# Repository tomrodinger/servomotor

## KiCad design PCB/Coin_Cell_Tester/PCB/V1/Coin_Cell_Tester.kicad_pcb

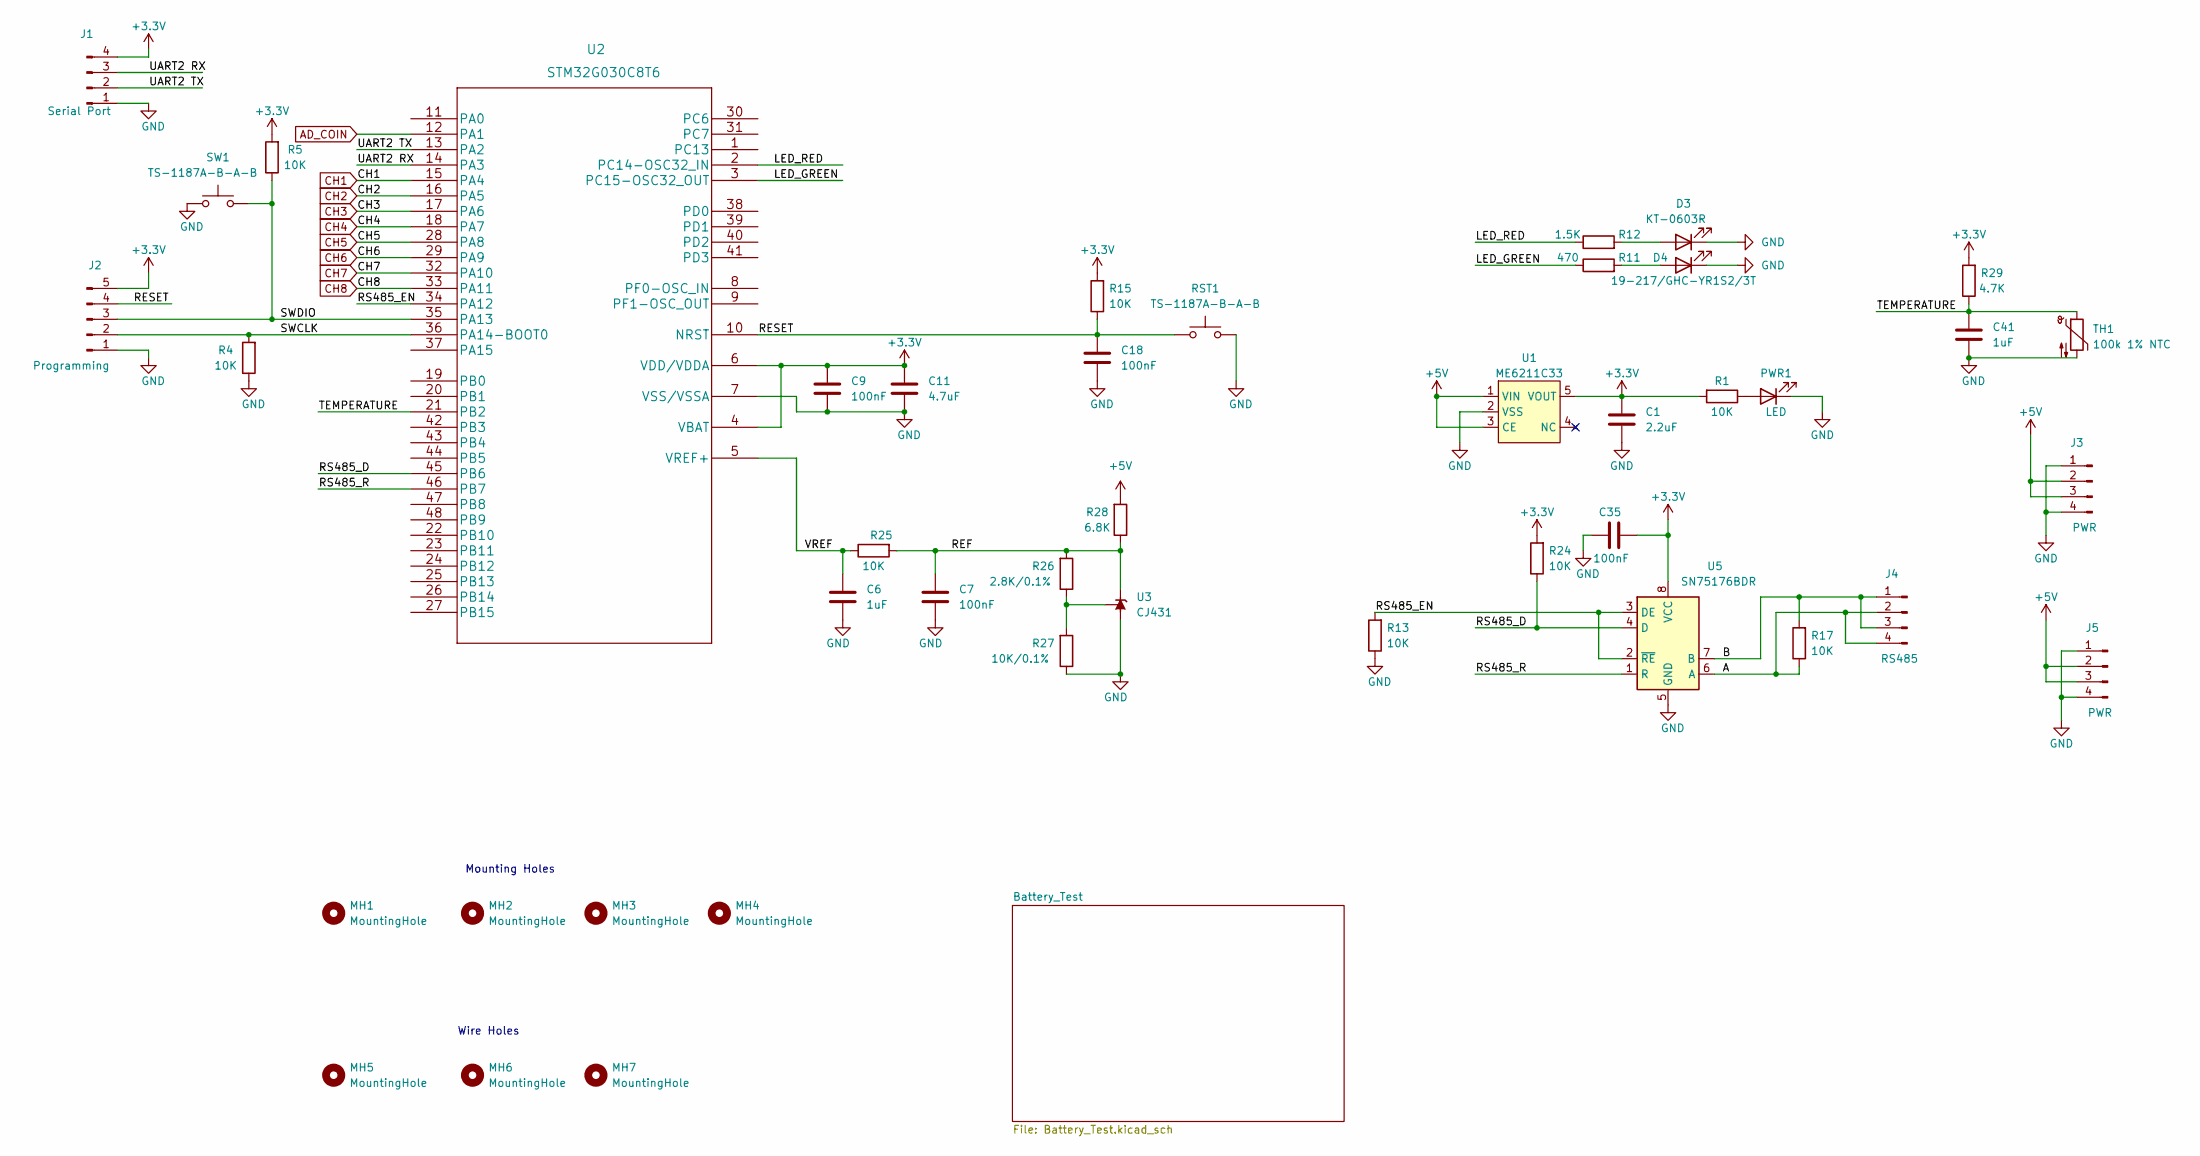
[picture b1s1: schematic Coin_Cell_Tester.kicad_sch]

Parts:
C1: 2.2uF; C_0603_1608Metric
C6, C41: 1uF; C_0603_1608Metric
C7, C9, C18, C35: 100nF; C_0603_1608Metric
C11: 4.7uF; C_0603_1608Metric
D3: KT-0603R; LED_0603_1608Metric
D4: 19-217/GHC-YR1S2/3T; LED_0603_1608Metric
J1: Serial Port; PinHeader_1x04_P2.54mm_Vertical
J2: Programming; PinHeader_1x05_P2.54mm_Vertical
J3, J5: PWR; PinHeader_1x04_P2.54mm_Vertical
J4: RS485; PinHeader_1x04_P2.54mm_Vertical
MH1, MH2, MH3, MH4: MountingHole; MountingHole_3.2mm_M3
MH5, MH6, MH7: MountingHole; Wire hole
PWR1: LED; LED_0603_1608Metric; LCSC PN C434420
R1, R4, R5, R13, R15, R17, R24, R25: 10K; R_0603_1608Metric
R11: 470; R_0603_1608Metric
R12: 1.5K; R_0603_1608Metric
R26: 2.8K/0.1%; R_0402_1005Metric; Mfr PN PTFR0402B2K80P9; LCSC C2692906
R27: 10K/0.1%; R_0603_1608Metric
R28: 6.8K; R_0603_1608Metric
R29: 4.7K; R_0603_1608Metric
RST1: TS-1187A-B-A-B; SW_SPST_TL3342
SW1: TS-1187A-B-A-B; SW_SPST_TL3342
TH1: 100k 1% NTC; R_0402_1005Metric
U1: ME6211C33; SOT-23-5; LCSC PN C82942
U2: STM32G030C8T6; LQFP-48_7x7mm_P0.5mm
U3: CJ431; SOT-23; LCSC C3113
U5: SN75176BDR; SOIC-8_3.9x4.9mm_P1.27mm

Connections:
+3V3: C1.1, C9.1, C11.1, C35.2, J1.4, J2.5, R1.2, R5.2, R15.2, R24.2, R29.2, U1.5 (VOUT), U2.4 (VBAT), U2.6 (VDD/VDDA), U5.8 (VCC)
+5V: J3.2, J3.3, J5.2, J5.3, R28.2, U1.1 (VIN), U1.3 (CE); also elsewhere on the board
/A: J4.2, J4.4, R17.1, U5.6 (A)
/B: J4.1, J4.3, R17.2, U5.7 (B)
/LED_GREEN: R11.1, U2.3 (PC15-OSC32_OUT)
/LED_RED: R12.1, U2.2 (PC14-OSC32_IN)
/REF: C7.1, R25.2, R26.2, R28.1, U3.1 (K)
/RESET: C18.1, J2.4, R15.1, RST1.1, U2.10 (NRST)
/RS485_D: R24.1, U2.45 (PB6), U5.4 (D)
/RS485_EN: R13.2, U2.34 (PA12), U5.2 (~RE), U5.3 (DE)
/RS485_R: U2.46 (PB7), U5.1 (R)
/SWCLK: J2.2, R4.2, U2.36 (PA14-BOOT0)
/SWDIO: J2.3, R5.1, SW1.2, U2.35 (PA13)
/TEMPERATURE: C41.1, R29.1, TH1.1, U2.21 (PB2)
/UART2 RX: J1.3, U2.14 (PA3)
/UART2 TX: J1.2, U2.13 (PA2)
/VREF: C6.1, R25.1, U2.5 (VREF+)
AD_COIN: U2.12 (PA1); also elsewhere on the board
CH1: U2.15 (PA4); also elsewhere on the board
CH2: U2.16 (PA5); also elsewhere on the board
CH3: U2.17 (PA6); also elsewhere on the board
CH4: U2.18 (PA7); also elsewhere on the board
CH5: U2.28 (PA8); also elsewhere on the board
CH6: U2.29 (PA9); also elsewhere on the board
CH7: U2.32 (PA10); also elsewhere on the board
CH8: U2.33 (PA11); also elsewhere on the board
GND: C1.2, C6.2, C7.2, C9.2, C11.2, C18.2, C35.1, C41.2, D3.1 (K), D4.1 (K), J1.1, J2.1, J3.1, J3.4, J5.1, J5.4, PWR1.1 (K), R4.1, R13.1, R27.1, RST1.2, SW1.1, TH1.2, U1.2 (VSS), U2.7 (VSS/VSSA), U3.3 (A), U5.5 (GND); also elsewhere on the board
unnamed: D3.2 (A), R12.2
unnamed: D4.2 (A), R11.2
unnamed: PWR1.2 (A), R1.1
unnamed: R26.1, R27.2, U3.2 (REF)

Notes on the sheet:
Mounting Holes
Wire Holes

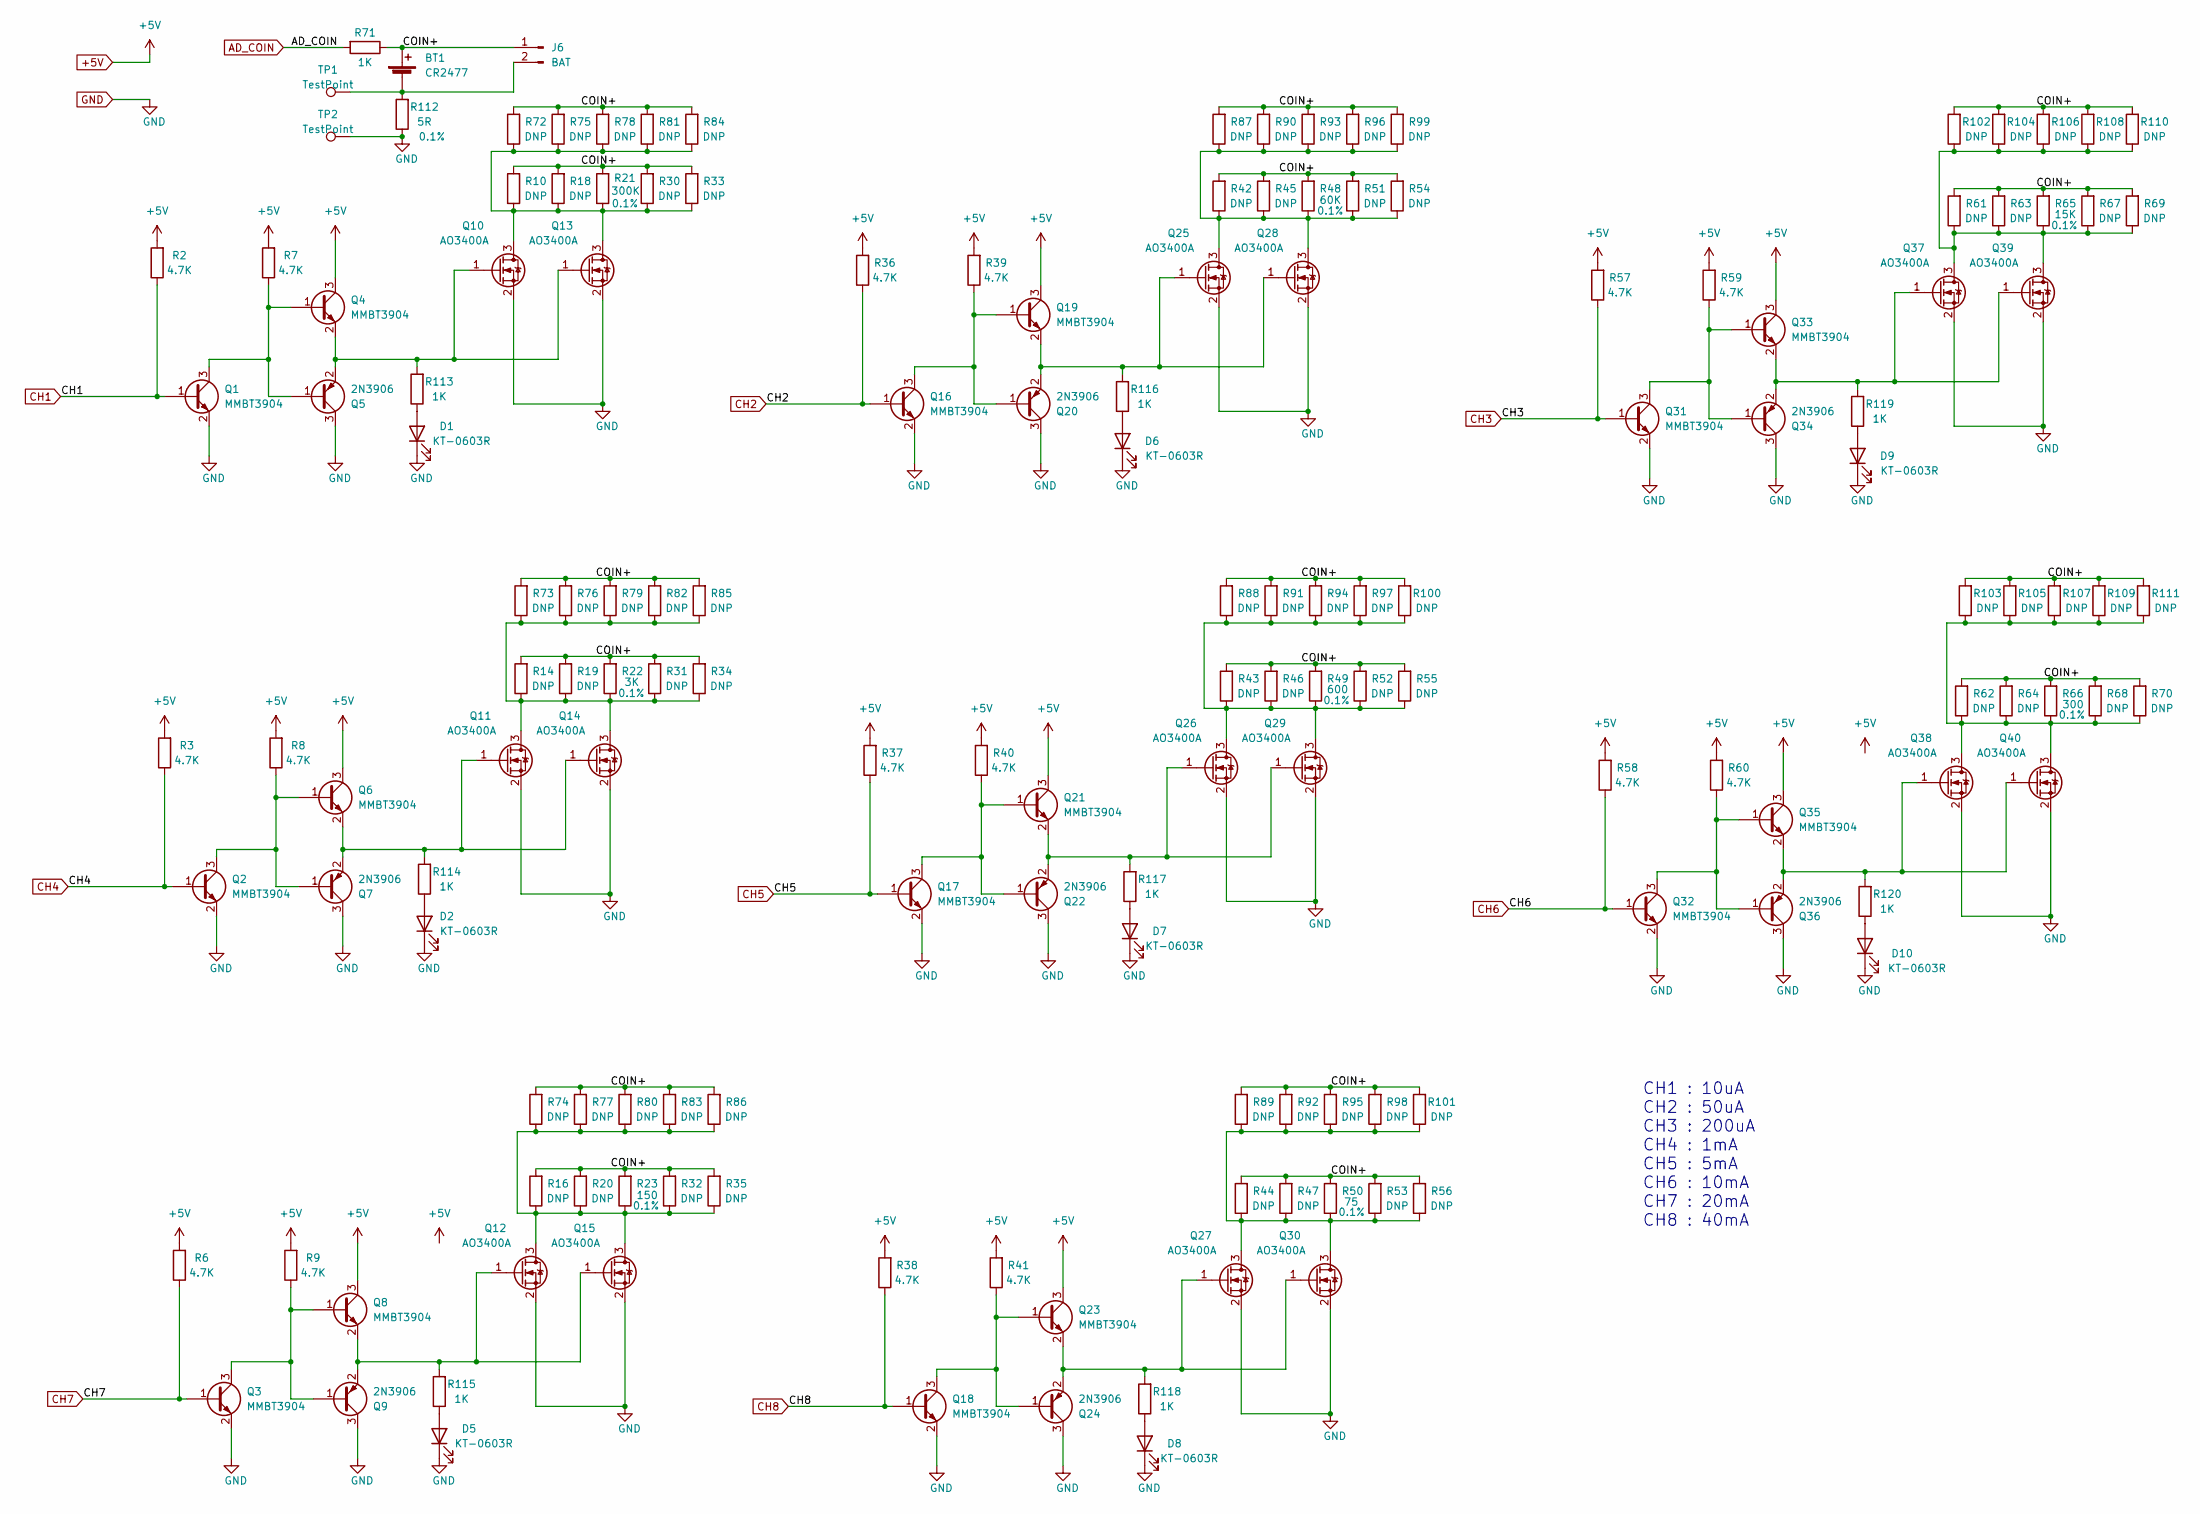
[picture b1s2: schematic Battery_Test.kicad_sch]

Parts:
BT1: CR2477; BatteryHolder_Keystone_105_1x2430; LCSC C969907
D1, D2, D5, D6, D7, D8, D9, D10: KT-0603R; LED_0603_1608Metric
J6: BAT; PinHeader_1x02_P2.54mm_Vertical
Q1, Q2, Q3, Q4, Q6, Q8, Q16, Q17, Q18, Q19, Q21, Q23, Q31, Q32, Q33, Q35: MMBT3904; SOT-23; LCSC C20526
Q5, Q7, Q9, Q20, Q22, Q24, Q34, Q36: 2N3906; SOT-23; LCSC C147294
Q10, Q11, Q12, Q13, Q14, Q15, Q25, Q26, Q27, Q28, Q29, Q30, Q37, Q38, Q39, Q40: AO3400A; SOT-23; LCSC C20917
R2, R3, R6, R7, R8, R9, R36, R37, R38, R39, R40, R41, R57, R58, R59, R60: 4.7K; R_0603_1608Metric
R10, R14, R16, R18, R19, R20, R30, R31, R32, R33, R34, R35, R42, R43, R44, R45, R46, R47, R51, R52, R53, R54, R55, R56, R61, R62, R63, R64, R67, R68, R69, R70: DNP; R_Axial_DIN0207_L6.3mm_D2.5mm_P10.16mm_Horizontal
R21: 300K; R_Axial_DIN0207_L6.3mm_D2.5mm_P10.16mm_Horizontal
R22: 3K; R_Axial_DIN0207_L6.3mm_D2.5mm_P10.16mm_Horizontal
R23: 150; R_Axial_DIN0207_L6.3mm_D2.5mm_P10.16mm_Horizontal
R48: 60K; R_Axial_DIN0207_L6.3mm_D2.5mm_P10.16mm_Horizontal
R49: 600; R_Axial_DIN0207_L6.3mm_D2.5mm_P10.16mm_Horizontal
R50: 75; R_Axial_DIN0207_L6.3mm_D2.5mm_P10.16mm_Horizontal
R65: 15K; R_Axial_DIN0207_L6.3mm_D2.5mm_P10.16mm_Horizontal
R66: 300; R_Axial_DIN0207_L6.3mm_D2.5mm_P10.16mm_Horizontal
R71, R113, R114, R115, R116, R117, R118, R119, R120: 1K; R_0603_1608Metric
R72, R73, R74, R87, R88, R89, R102, R103: DNP; R_0402_1005Metric
R75, R76, R77, R90, R91, R92, R104, R105: DNP; R_0603_1608Metric
R78, R79, R80, R93, R94, R95, R106, R107: DNP; R_0805_2012Metric
R81, R82, R83, R96, R97, R98, R108, R109: DNP; R_1206_3216Metric
R84, R85, R86, R99, R100, R101, R110, R111: DNP; R_1210_3225Metric
R112: 5R; R_Axial_DIN0207_L6.3mm_D2.5mm_P10.16mm_Horizontal
TP1, TP2: TestPoint; TestPoint_Plated_Hole_D2.0mm

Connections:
+5V: Q4.3 (C), Q6.3 (C), Q8.3 (C), Q19.3 (C), Q21.3 (C), Q23.3 (C), Q33.3 (C), Q35.3 (C), R2.2, R3.2, R6.2, R7.2, R8.2, R9.2, R36.2, R37.2, R38.2, R39.2, R40.2, R41.2, R57.2, R58.2, R59.2, R60.2; also elsewhere on the board
/Battery_Test/COIN+: BT1.1 (+), J6.1, R10.2, R14.2, R16.2, R18.2, R19.2, R20.2, R21.2, R22.2, R23.2, R30.2, R31.2, R32.2, R33.2, R34.2, R35.2, R42.2, R43.2, R44.2, R45.2, R46.2, R47.2, R48.2, R49.2, R50.2, R51.2, R52.2, R53.2, R54.2, R55.2, R56.2, R61.2, R62.2, R63.2, R64.2, R65.2, R66.2, R67.2, R68.2, R69.2, R70.2, R71.1, R72.2, R73.2, R74.2, R75.2, R76.2, R77.2, R78.2, R79.2, R80.2, R81.2, R82.2, R83.2, R84.2, R85.2, R86.2, R87.2, R88.2, R89.2, R90.2, R91.2, R92.2, R93.2, R94.2, R95.2, R96.2, R97.2, R98.2, R99.2, R100.2, R101.2, R102.2, R103.2, R104.2, R105.2, R106.2, R107.2, R108.2, R109.2, R110.2, R111.2
AD_COIN: R71.2; also elsewhere on the board
CH1: Q1.1 (B), R2.1; also elsewhere on the board
CH2: Q16.1 (B), R36.1; also elsewhere on the board
CH3: Q31.1 (B), R57.1; also elsewhere on the board
CH4: Q2.1 (B), R3.1; also elsewhere on the board
CH5: Q17.1 (B), R37.1; also elsewhere on the board
CH6: Q32.1 (B), R58.1; also elsewhere on the board
CH7: Q3.1 (B), R6.1; also elsewhere on the board
CH8: Q18.1 (B), R38.1; also elsewhere on the board
GND: D1.1 (K), D2.1 (K), D5.1 (K), D6.1 (K), D7.1 (K), D8.1 (K), D9.1 (K), D10.1 (K), Q1.2 (E), Q2.2 (E), Q3.2 (E), Q5.3 (C), Q7.3 (C), Q9.3 (C), Q10.2 (S), Q11.2 (S), Q12.2 (S), Q13.2 (S), Q14.2 (S), Q15.2 (S), Q16.2 (E), Q17.2 (E), Q18.2 (E), Q20.3 (C), Q22.3 (C), Q24.3 (C), Q25.2 (S), Q26.2 (S), Q27.2 (S), Q28.2 (S), Q29.2 (S), Q30.2 (S), Q31.2 (E), Q32.2 (E), Q34.3 (C), Q36.3 (C), Q37.2 (S), Q38.2 (S), Q39.2 (S), Q40.2 (S), R112.1, TP2.1; also elsewhere on the board
unnamed: BT1.2 (-), J6.2, R112.2, TP1.1
unnamed: D1.2 (A), R113.1
unnamed: D2.2 (A), R114.1
unnamed: D6.2 (A), R116.1
unnamed: Q1.3 (C), Q4.1 (B), Q5.1 (B), R7.1
unnamed: Q2.3 (C), Q6.1 (B), Q7.1 (B), R8.1
unnamed: Q3.3 (C), Q8.1 (B), Q9.1 (B), R9.1
unnamed: Q4.2 (E), Q5.2 (E), Q10.1 (G), Q13.1 (G), R113.2
unnamed: Q10.3 (D), Q13.3 (D), R10.1, R18.1, R21.1, R30.1, R33.1, R72.1, R75.1, R78.1, R81.1, R84.1
unnamed: Q6.2 (E), Q7.2 (E), Q11.1 (G), Q14.1 (G), R114.2
unnamed: Q11.3 (D), Q14.3 (D), R14.1, R19.1, R22.1, R31.1, R34.1, R73.1, R76.1, R79.1, R82.1, R85.1
unnamed: Q8.2 (E), Q9.2 (E), Q12.1 (G), Q15.1 (G), R115.2
unnamed: Q12.3 (D), Q15.3 (D), R16.1, R20.1, R23.1, R32.1, R35.1, R74.1, R77.1, R80.1, R83.1, R86.1
unnamed: Q16.3 (C), Q19.1 (B), Q20.1 (B), R39.1
unnamed: Q17.3 (C), Q21.1 (B), Q22.1 (B), R40.1
unnamed: Q18.3 (C), Q23.1 (B), Q24.1 (B), R41.1
unnamed: Q19.2 (E), Q20.2 (E), Q25.1 (G), Q28.1 (G), R116.2
unnamed: Q21.2 (E), Q22.2 (E), Q26.1 (G), Q29.1 (G), R117.2
unnamed: Q23.2 (E), Q24.2 (E), Q27.1 (G), Q30.1 (G), R118.2
unnamed: Q25.3 (D), Q28.3 (D), R42.1, R45.1, R48.1, R51.1, R54.1, R87.1, R90.1, R93.1, R96.1, R99.1
unnamed: Q26.3 (D), Q29.3 (D), R43.1, R46.1, R49.1, R52.1, R55.1, R88.1, R91.1, R94.1, R97.1, R100.1
unnamed: Q27.3 (D), Q30.3 (D), R44.1, R47.1, R50.1, R53.1, R56.1, R89.1, R92.1, R95.1, R98.1, R101.1
unnamed: Q31.3 (C), Q33.1 (B), Q34.1 (B), R59.1
unnamed: Q32.3 (C), Q35.1 (B), Q36.1 (B), R60.1
unnamed: Q33.2 (E), Q34.2 (E), Q37.1 (G), Q39.1 (G), R119.2
unnamed: Q35.2 (E), Q36.2 (E), Q38.1 (G), Q40.1 (G), R120.2
unnamed: Q37.3 (D), Q39.3 (D), R61.1, R63.1, R65.1, R67.1, R69.1, R102.1, R104.1, R106.1, R108.1, R110.1
unnamed: Q38.3 (D), Q40.3 (D), R62.1, R64.1, R66.1, R68.1, R70.1, R103.1, R105.1, R107.1, R109.1, R111.1
unnamed: D5.2 (A), R115.1
unnamed: D7.2 (A), R117.1
unnamed: D8.2 (A), R118.1
unnamed: D9.2 (A), R119.1
unnamed: D10.2 (A), R120.1

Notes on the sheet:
CH1 : 10uA CH2 : 50uA CH3 : 200uA CH4 : 1mA CH5 : 5mA CH6 : 10mA CH7 : 20mA CH8 : 40mA

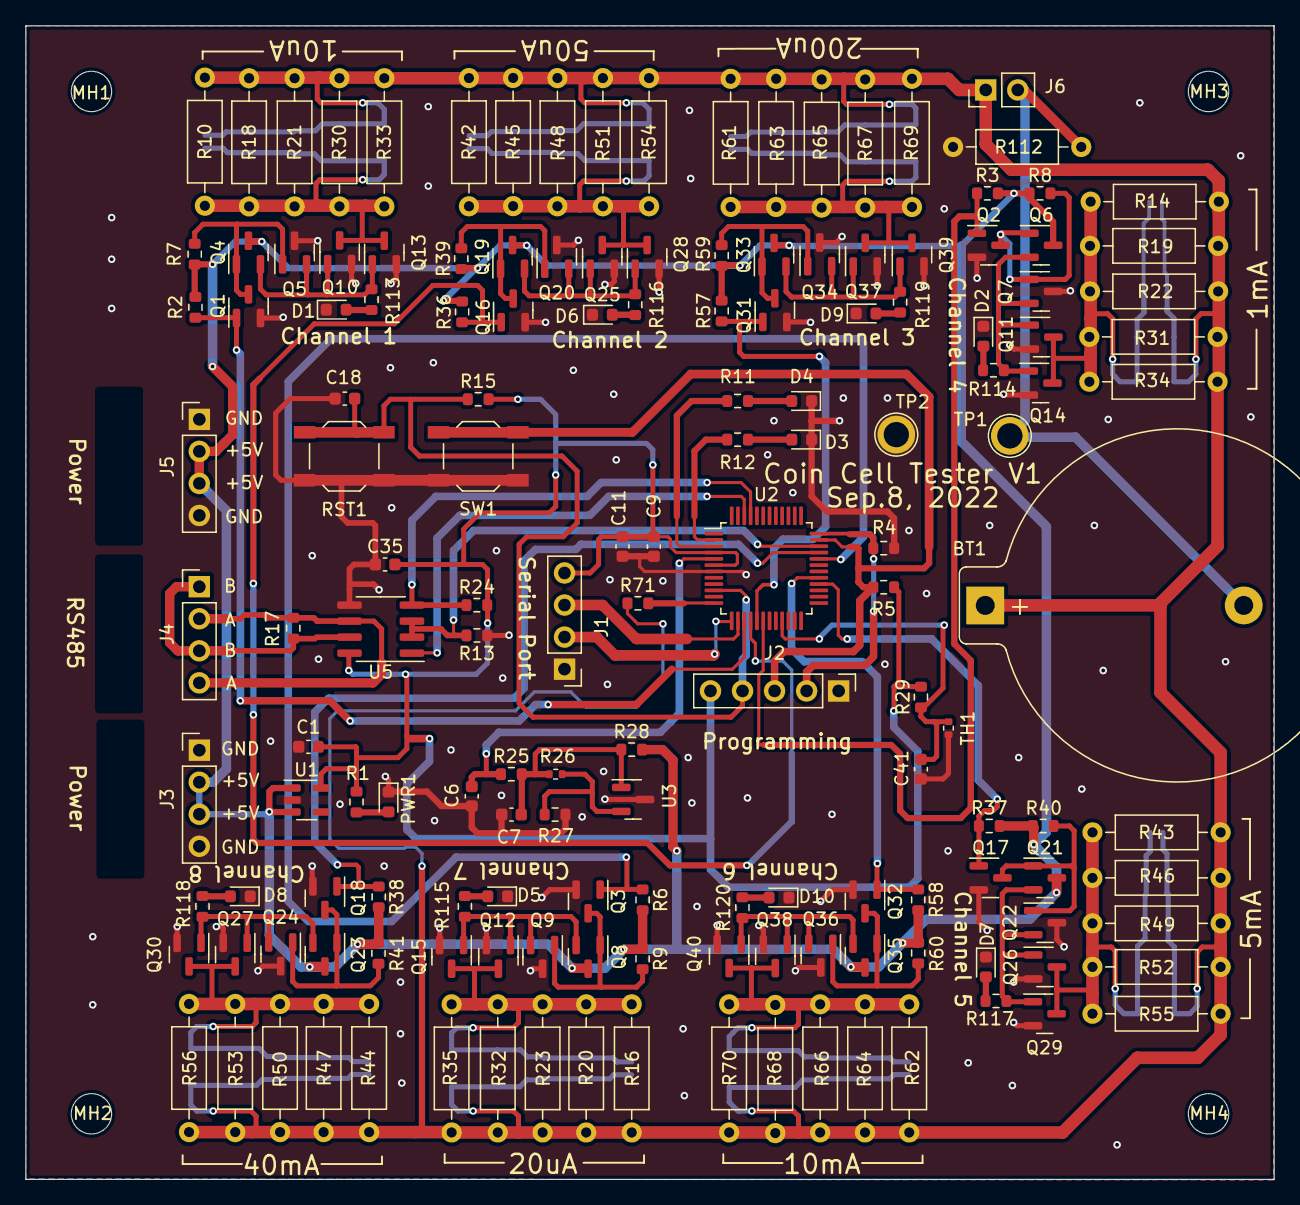
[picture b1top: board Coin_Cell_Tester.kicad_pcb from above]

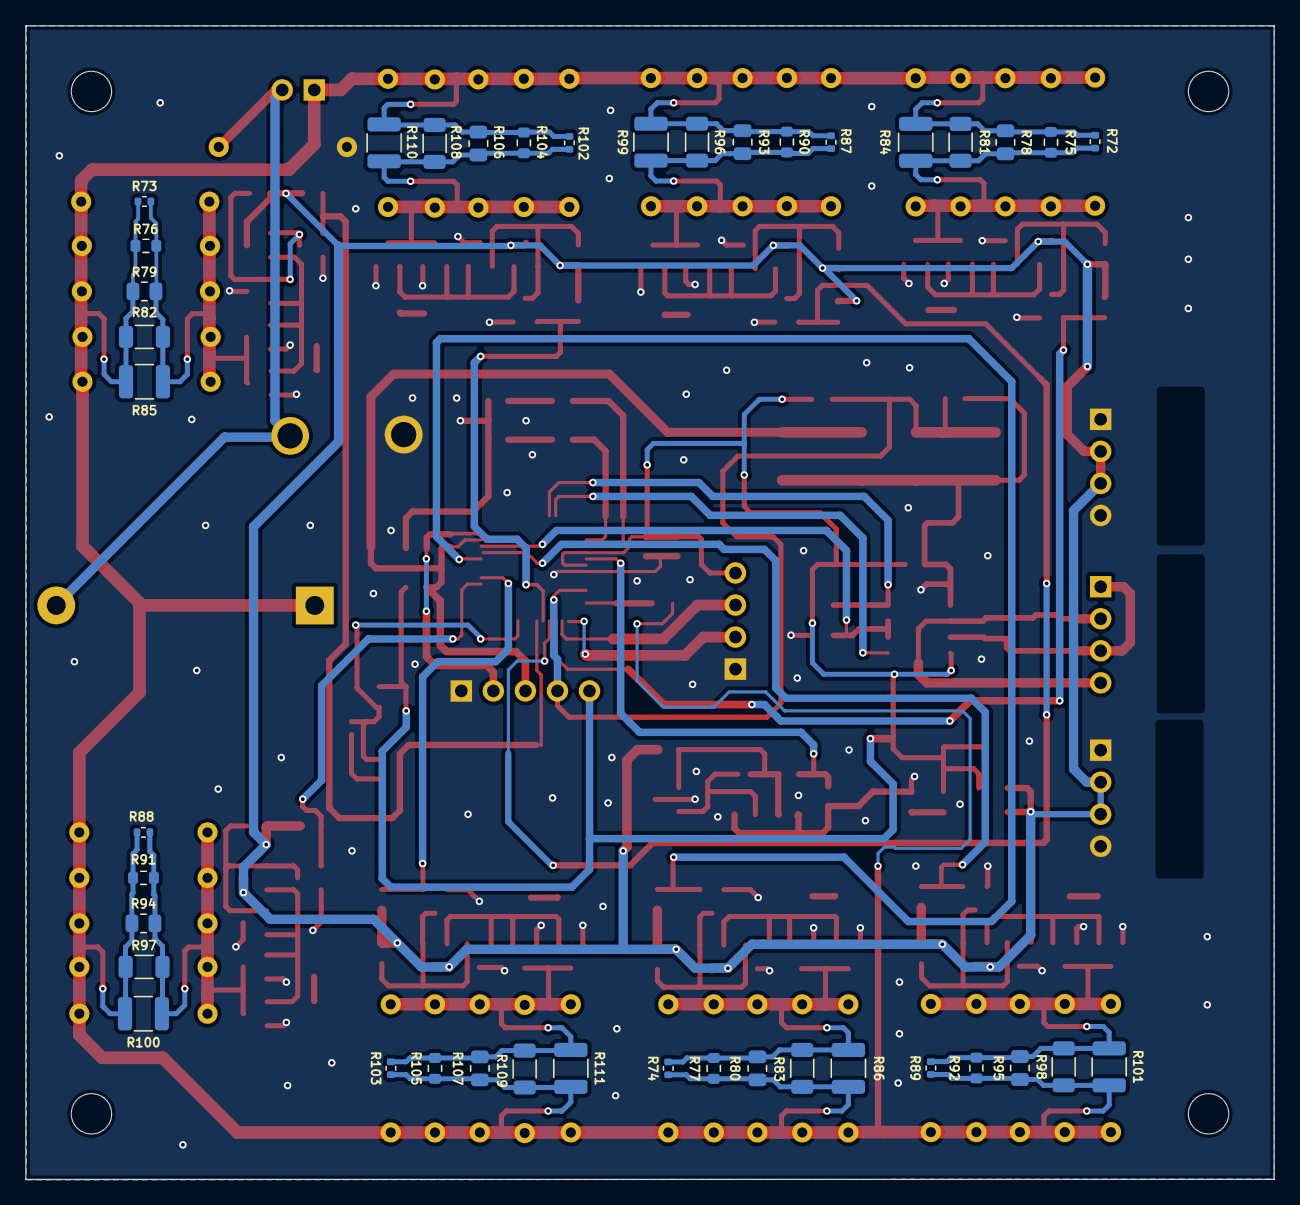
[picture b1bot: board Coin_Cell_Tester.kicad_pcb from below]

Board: 2 copper layers, 98.9 x 91.4 mm, 202 parts (40 on the bottom side), 65 nets.

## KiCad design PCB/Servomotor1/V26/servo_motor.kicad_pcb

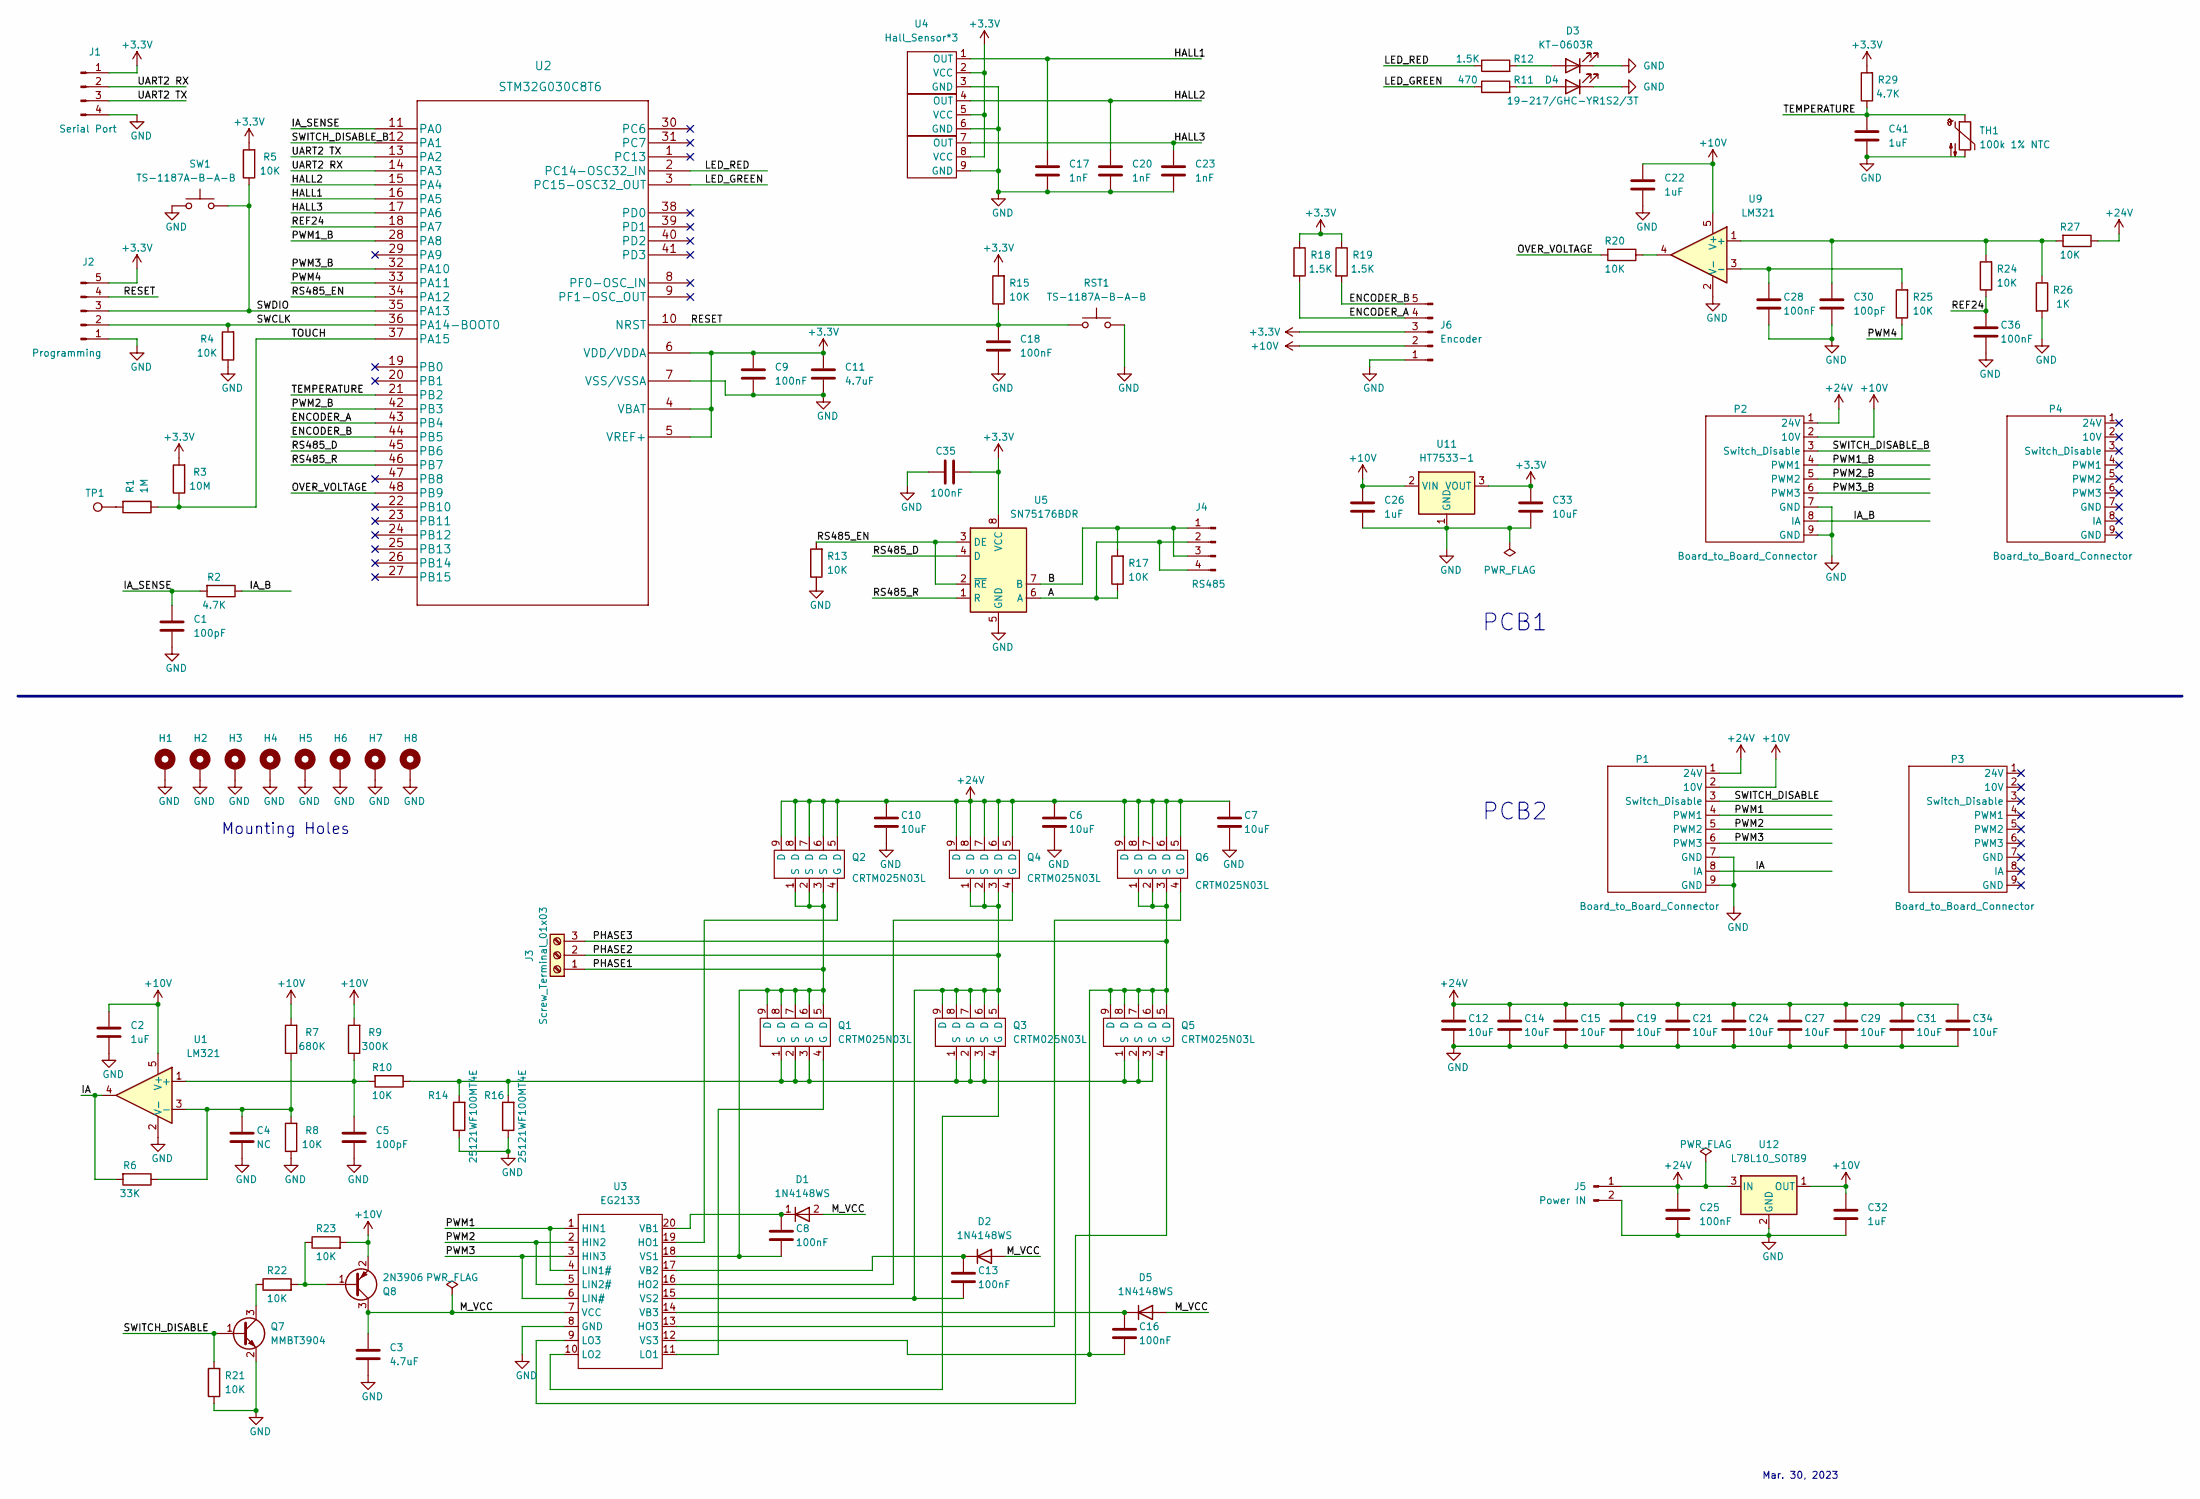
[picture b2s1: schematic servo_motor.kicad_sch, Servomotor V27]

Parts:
C1, C5, C30: 100pF; C_0603_1608Metric; MPN CL10C101JB8NNNC; LCSC C14858
C2, C22, C26, C32, C41: 1uF; C_0603_1608Metric; MPN CL10A105KB8NNNC; LCSC C15849
C3, C11: 4.7uF; C_0603_1608Metric; MPN CL10A475KO8NNNC; LCSC C19666
C4: NC; C_0603_1608Metric
C6, C7, C10, C12, C14, C15, C19, C21, C24, C27, C29, C31, C34: 10uF; C_0805_2012Metric; MPN GRM21BR61H106KE43L; LCSC C440198
C8, C9, C13, C16, C18, C25, C28, C35, C36: 100nF; C_0603_1608Metric; MPN CC0603KRX7R9BB104; LCSC C14663
C17, C20, C23: 1nF; C_0603_1608Metric; MPN CL10B102KB8NNNC; LCSC C1588
C33: 10uF; C_0603_1608Metric; MPN CL10A106KP8NNNC; LCSC C19702
D1, D2, D5: 1N4148WS; D_SOD-323; MPN 1N4148WS; LCSC C2128
D3: KT-0603R; LED_0603_1608Metric; MPN 1N4148WS; LCSC C2286
D4: 19-217/GHC-YR1S2/3T; LED_0603_1608Metric; MPN KT-0603R; LCSC C72043
H1, H2, H3, H4, H5, H6, H7, H8: MountingHole_Pad; Mounting Hole 3.5mm
J1: Serial Port; PinHeader_1x04_P2.54mm_Vertical; MPN PZ254V-11-04P; LCSC C2691448
J2: Programming; PinHeader_1x05_P2.54mm_Vertical; MPN PZ254V-11-05P; LCSC C492404
J3: Screw_Terminal_01x03; MOTOR
J4: RS485; PinHeader_1x04_P2.54mm_Vertical; MPN PZ254V-11-04P; LCSC C2691448
J5: Power IN; TerminalBlock_bornier-2_P5.08mm; MPN WJ500V-5.08-2P; LCSC C8465
J6: Encoder; PinHeader_1x05_P2.54mm_Vertical; MPN PZ254V-11-05P; LCSC C492404
P1, P3: Board_to_Board_Connector; board_to_board_male
P2, P4: Board_to_Board_Connector; board_to_board_female
Q1, Q2, Q3, Q4, Q5, Q6: CRTM025N03L; MPN CRTM025N03L; LCSC C467170
Q7: MMBT3904; SOT-23; MPN MMBT3904; LCSC C20526
Q8: 2N3906; SOT-23; MPN 2N3906S-RTK/P; LCSC C147294
R1: 1M; R_0603_1608Metric; MPN 0603WAF1004T5E; LCSC C22935
R2, R29: 4.7K; R_0603_1608Metric; MPN 0603WAF4701T5E; LCSC C23162
R3: 10M; R_0603_1608Metric; MPN 0603WAF1005T5E; LCSC C7250
R4, R5, R8, R10, R13, R15, R17, R20, R21, R22, R23, R24, R25, R27: 10K; R_0603_1608Metric; MPN 0603WAF1002T5E; LCSC C25804
R6: 33K; R_0603_1608Metric; MPN 0603WAF3302T5E; LCSC C4216
R7: 680K; R_0603_1608Metric; MPN 0603WAF6803T5E; LCSC C25822
R9: 300K; R_0603_1608Metric; MPN 0603WAF3003T5E; LCSC C23024
R11: 470; R_0603_1608Metric; MPN 0603WAF4700T5E; LCSC C23179
R12, R18, R19: 1.5K; R_0603_1608Metric; MPN 0603WAF1501T5E; LCSC C22843
R14, R16: 25121WF100MT4E; R_2512_6332Metric; MPN 25121WF100MT4E; LCSC C127692
R26: 1K; R_0603_1608Metric; MPN 0603WAF1001T5E; LCSC C21190
RST1: TS-1187A-B-A-B; SW_SPST_TL3342; MPN TS-1187A-B-A-B; LCSC C318884
SW1: TS-1187A-B-A-B; SW_SPST_TL3342; MPN TS-1187A-B-A-B; LCSC C318884
TH1: 100k 1% NTC; R_0402_1005Metric; MPN NCP15WF104F03RC; LCSC C77130
TP1: TestPoint; TestPoint 6mm
U1, U9: LM321; SOT-23-5; MPN LM321LVIDBVR; LCSC C471859
U2: STM32G030C8T6; MPN STM32G030C8T6; LCSC C529329
U3: EG2133; TSSOP-20_4.4x6.5mm_P0.65mm; MPN EG2133; LCSC C190343
U4: Hall_Sensor*3; hall_sensor_3
U5: SN75176BDR; SOIC-8_3.9x4.9mm_P1.27mm; MPN SN75176BDR; LCSC C7063
U11: HT7533-1; SOT-89-3; MPN HT7533-1; LCSC C14289
U12: L78L10_SOT89; SOT-89-3; MPN 78L10; LCSC C122848

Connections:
+3V3: C9.1, C11.1, C33.1, C35.2, J1.1, J2.5, J6.3, R3.2, R5.2, R15.2, R18.1, R19.1, R29.2, U2.4 (VBAT), U2.5 (VREF+), U2.6 (VDD/VDDA), U4.2 (VCC), U4.5 (VCC), U4.8 (VCC), U5.8 (VCC), U11.3 (VOUT)
+24V: C6.1, C7.1, C10.1, C12.1, C14.1, C15.1, C19.1, C21.1, C24.1, C25.1, C27.1, C29.1, C31.1, C34.1, J5.1, P1.1 (24V), P2.1 (24V), Q2.5 (D), Q2.6 (D), Q2.7 (D), Q2.8 (D), Q2.9 (D), Q4.5 (D), Q4.6 (D), Q4.7 (D), Q4.8 (D), Q4.9 (D), Q6.5 (D), Q6.6 (D), Q6.7 (D), Q6.8 (D), Q6.9 (D), R27.1, U12.3 (IN)
/A: J4.2, J4.4, R17.1, U5.6 (A)
/B: J4.1, J4.3, R17.2, U5.7 (B)
/ENCODER_A: J6.4, R18.2, U2.43 (PB4)
/ENCODER_B: J6.5, R19.2, U2.44 (PB5)
/HALL1: C17.1, U2.16 (PA5), U4.1 (OUT)
/HALL2: C20.1, U2.15 (PA4), U4.4 (OUT)
/HALL3: C23.1, U2.17 (PA6), U4.7 (OUT)
/IA: P1.8 (IA), R6.2, U1.4
/IA_B: P2.8 (IA), R2.1
/IA_SENSE: C1.1, R2.2, U2.11 (PA0)
/LED_GREEN: R11.1, U2.3 (PC15-OSC32_OUT)
/LED_RED: R12.1, U2.2 (PC14-OSC32_IN)
/OVER_VOLTAGE: R20.2, U2.48 (PB9)
/PHASE1: C8.2, J3.1, Q1.5 (D), Q1.6 (D), Q1.7 (D), Q1.8 (D), Q1.9 (D), Q2.1 (S), Q2.2 (S), Q2.3 (S), U3.18 (VS1)
/PHASE2: C13.2, J3.2, Q3.5 (D), Q3.6 (D), Q3.7 (D), Q3.8 (D), Q3.9 (D), Q4.1 (S), Q4.2 (S), Q4.3 (S), U3.15 (VS2)
/PHASE3: C16.2, J3.3, Q5.5 (D), Q5.6 (D), Q5.7 (D), Q5.8 (D), Q5.9 (D), Q6.1 (S), Q6.2 (S), Q6.3 (S), U3.12 (VS3)
/PWM1: P1.4 (PWM1), U3.1 (HIN1), U3.4 (LIN1#)
/PWM1_B: P2.4 (PWM1), U2.28 (PA8)
/PWM2: P1.5 (PWM2), U3.2 (HIN2), U3.5 (LIN2#)
/PWM2_B: P2.5 (PWM2), U2.42 (PB3)
/PWM3: P1.6 (PWM3), U3.3 (HIN3), U3.6 (LIN#)
/PWM3_B: P2.6 (PWM3), U2.32 (PA10)
/PWM4: R25.1, U2.33 (PA11)
/REF24: C36.1, R24.1, U2.18 (PA7)
/RESET: C18.1, J2.4, R15.1, RST1.1, U2.10 (NRST)
/RS485_D: U2.45 (PB6), U5.4 (D)
/RS485_EN: R13.2, U2.34 (PA12), U5.2 (~RE), U5.3 (DE)
/RS485_R: U2.46 (PB7), U5.1 (R)
/SWCLK: J2.2, R4.2, U2.36 (PA14-BOOT0)
/SWDIO: J2.3, R5.1, SW1.2, U2.35 (PA13)
/SWITCH_DISABLE: P1.3 (Switch_Disable), Q7.1 (B), R21.2
/SWITCH_DISABLE_B: P2.3 (Switch_Disable), U2.12 (PA1)
/TEMPERATURE: C41.1, R29.1, TH1.1, U2.21 (PB2)
/TOUCH: R1.1, R3.1, U2.37 (PA15)
/UART2 RX: J1.2, U2.14 (PA3)
/UART2 TX: J1.3, U2.13 (PA2)
GND: C1.2, C2.2, C3.2, C4.2, C5.2, C6.2, C7.2, C9.2, C10.2, C11.2, C12.2, C14.2, C15.2, C17.2, C18.2, C19.2, C20.2, C21.2, C22.2, C23.2, C24.2, C25.2, C26.2, C27.2, C28.2, C29.2, C30.2, C31.2, C32.2, C33.2, C34.2, C35.1, C36.2, C41.2, D3.1 (K), D4.1 (K), H1.1, H2.1, H3.1, H4.1, H5.1, H6.1, H7.1, H8.1, J1.4, J2.1, J5.2, J6.1, P1.7 (GND), P1.9 (GND), P2.7 (GND), P2.9 (GND), Q7.2 (E), R4.1, R8.1, R13.1, R14.1, R16.1, R21.1, R26.2, RST1.2, SW1.1, TH1.2, U1.2 (V-), U2.7 (VSS/VSSA), U3.8 (GND), U4.3 (GND), U4.6 (GND), U4.9 (GND), U5.5 (GND), U9.2 (V-), U11.1 (GND), U12.2 (GND)
unnamed: C4.1, R6.1, R7.1, R8.2, U1.3 (-)
unnamed: C5.1, R9.1, R10.2, U1.1 (+)
unnamed: C8.1, D1.1 (K), U3.20 (VB1)
unnamed: C13.1, D2.1 (K), U3.17 (VB2)
unnamed: C16.1, D5.1 (K), U3.14 (VB3)
unnamed: C28.1, R25.2, U9.3 (-)
unnamed: C30.1, R24.2, R26.1, R27.2, U9.1 (+)
unnamed: D3.2 (A), R12.2
unnamed: D4.2 (A), R11.2
unnamed: Q1.1 (S), Q1.2 (S), Q1.3 (S), Q3.1 (S), Q3.2 (S), Q3.3 (S), Q5.1 (S), Q5.2 (S), Q5.3 (S), R10.1, R14.2, R16.2
unnamed: Q1.4 (G), U3.11 (LO1)
unnamed: Q2.4 (G), U3.19 (HO1)
unnamed: Q3.4 (G), U3.10 (LO2)
unnamed: Q4.4 (G), U3.16 (HO2)
unnamed: Q5.4 (G), U3.9 (LO3)
unnamed: Q6.4 (G), U3.13 (HO3)
unnamed: Q7.3 (C), R22.1
unnamed: Q8.1 (B), R22.2, R23.1
unnamed: R1.2, TP1.1
unnamed: R20.1, U9.4

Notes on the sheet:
Mar. 30, 2023
PCB1
Mounting Holes
PCB2

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

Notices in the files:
parts and their libraries:
Copyright 2021 Accelerated Designs. All rights reserved.
